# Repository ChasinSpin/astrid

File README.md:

# Astrid (ASTro Imaging Device)

## Introduction

Astrid is a device, software and hardware to record astronomical Occultations, Transits, Eclipses (OTE), and Astrophotography.  Occultations are rare, and having equipment for rare events means that the equipment is unused at other times.  The concept of Astrid is that the device can be used as a general astrophotography camera when occultation work is not being done.  

Astrid compromises of:

* Raspberry Pi 4 Model B - 8GB (4GB untested)
* IMX296 Mono Camera [CAM-MIPI296RAW-Trigger](https://www.inno-maker.com/product/cam-mipi296raw-trigger/)
* [OTEStamper](OTEStamper) Timing board
* Software and Firmware

Astrid has the following features:

* Highly accurate frame timestamping for occultations using GPS
* Global Shutter (Sony IMX296 Sensor Mono)
* Controlled over VNC from Tablet/Computer/Phone (one can control many Astrids)
* Can be paired with a telescope or camera lens
* Audit trail for video
* GPS Position/Altitude
* Plate Solving
* Mount support: [IndiLib](https://indilib.org)
* Focuser support: [IndiLib](https://indilib.org) - Coming Soon
* Goto
* Star Detection
* Stretch
* Uncompressed raw data/video
* .fits file (photos)
* [Raw Astro Video Format (RAVF)](https://github.com/ChasinSpin/ravf) files for video (occultations)
* [PyMovie Support](https://github.com/ChasinSpin/pymovie)
* Dithering
* Multiple Subs
* Occelmnt support
* Occultation metrics
* Unattended Pre-Pointing

## PyMovie

Astrid [Raw Astro Video Format (RAVF)](https://github.com/ChasinSpin/ravf) can be loaded in PyMovie for analysis, using [RAVF PyMovie](https://github.com/ChasinSpin/pymovie).

## Documentation

[Documentation](docs/README.md)

## Obtaining Astrid

Astrid is now being supplied fully built and ready to go from IOTA.  Please see:
[https://occultations.org/astrid-details-and-ordering-page/
](https://occultations.org/astrid-details-and-ordering-page/)

Please note that although Open Source software is free, it is also generally considered good practice to support the time / resources that are donated by authors by purchasing through approved channels like IOTA where available.  That way the software/hardware can continue to be developed. Limited support is also available if one of the approved boards is purchased. 

If you build the board yourself, or it was obtained from another, we are unable to provide support. There has been instances of people making boards, selling them to others for profit and then expecting assistance for free.  We do not have the resources to support these types of ventures.

## Credits

* Steve Preston of IOTA for his invaluable assistance
* Bill Yeung for testing
* Bob Anderson for PyMovie
* Dave Herald - Star Catalogs and Occelmnt
* Hristo Pavlov for OWCloud

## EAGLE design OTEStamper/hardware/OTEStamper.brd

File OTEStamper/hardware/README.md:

## Version 0.9b
	
* Initial

## Version 0.9c

* No electrical changes.
* Moved label for D1 below diode and clarified orientation for the Buck Regulator to make it less likely to assemble wrong way round.

## Version 1.0.0
	
* Added HOT label around buck convertor and back protection FET
* Removed 4 pin flat flex to camera board
* Moved JP2 right to allow clearance of U2
* Moved buzzer to bottom of the board and rotated 45 to make room for 150uF capacitor
* Added 150uF capacitor to limit surge current to regulator
* Moved Fan header so header pins easily clear GPS
* Added JST 2 Pin Connector For Different 12V Source
* Changed Q1/Q2 to MMBT2222A-TP for increased fan current upto 500mA

## Version 1.0.0 (no board revision)

Extended monostable duration from 1.2us to 1ms to account for
different versions of the camera module with varying XVS pulse lengths, which
can cause multiple pulses for each XVS signal:

 * Changed R18 from 1K to 10K
 * Changes C12 from 1nF to 0.1uF

## Future Ideas

1. Maybe look at switching out back protection FET to one with lower RDS as the voltage drop across is large at high currents (buck can keep up fine).

## PSU Characterisation

1. Voltage range is 7.5 - 18V, specified range to the user is 12V-15V @ 4A

2. Voltage dropout occurs at 7.5V

3. Buck starts to current limit (switch the PSU on and off) at 4.1A

4. Max temperature ofr the bucks convert (4A @ 18V) is 130C

5. Damage to the buck convertor will occur at 20V

6. Fuse never gets triggered during normal use.  Would only get trigger if there was failure on the board itself.

| PSU Output | Supply Input | Temperature |
| ---------- | ------------ | ----------- |
| 0.2A @ 5.04V | 0.062A @ 18V | Room |
| 1A @ 5.02V | 0.304A @ 18V | 42C |
| 2A @ 4.97V | 0.604A @ 18V | 57C |
| 3A @ 4.89V | 0.920A @ 18V | 85C |
| 4A @ 4.79V | 1.243A @ 18V | 125C |

## Testing

1. Power at 12V at current limit 40mA, power usage should be approx 25-30mA, GPS LED should be on
2. Test voltage TP1 = Just above 5V
3. Test voltage TP2 = 5V
4. Test in Software with Raspberry Pi and Camera Connected:

	a) Install firmware
	
		make reset
		make writefuses
		make install

	b) Test Buzzer and Fan:
 	
		cd ~/astrid/OTEStamper/test
		./spitest.py
		
	c) Test GPS (and check voltage monitoring)
	
		./spitest_gps.py
	
	d) Record video and check all status buttons are green and video is recorded

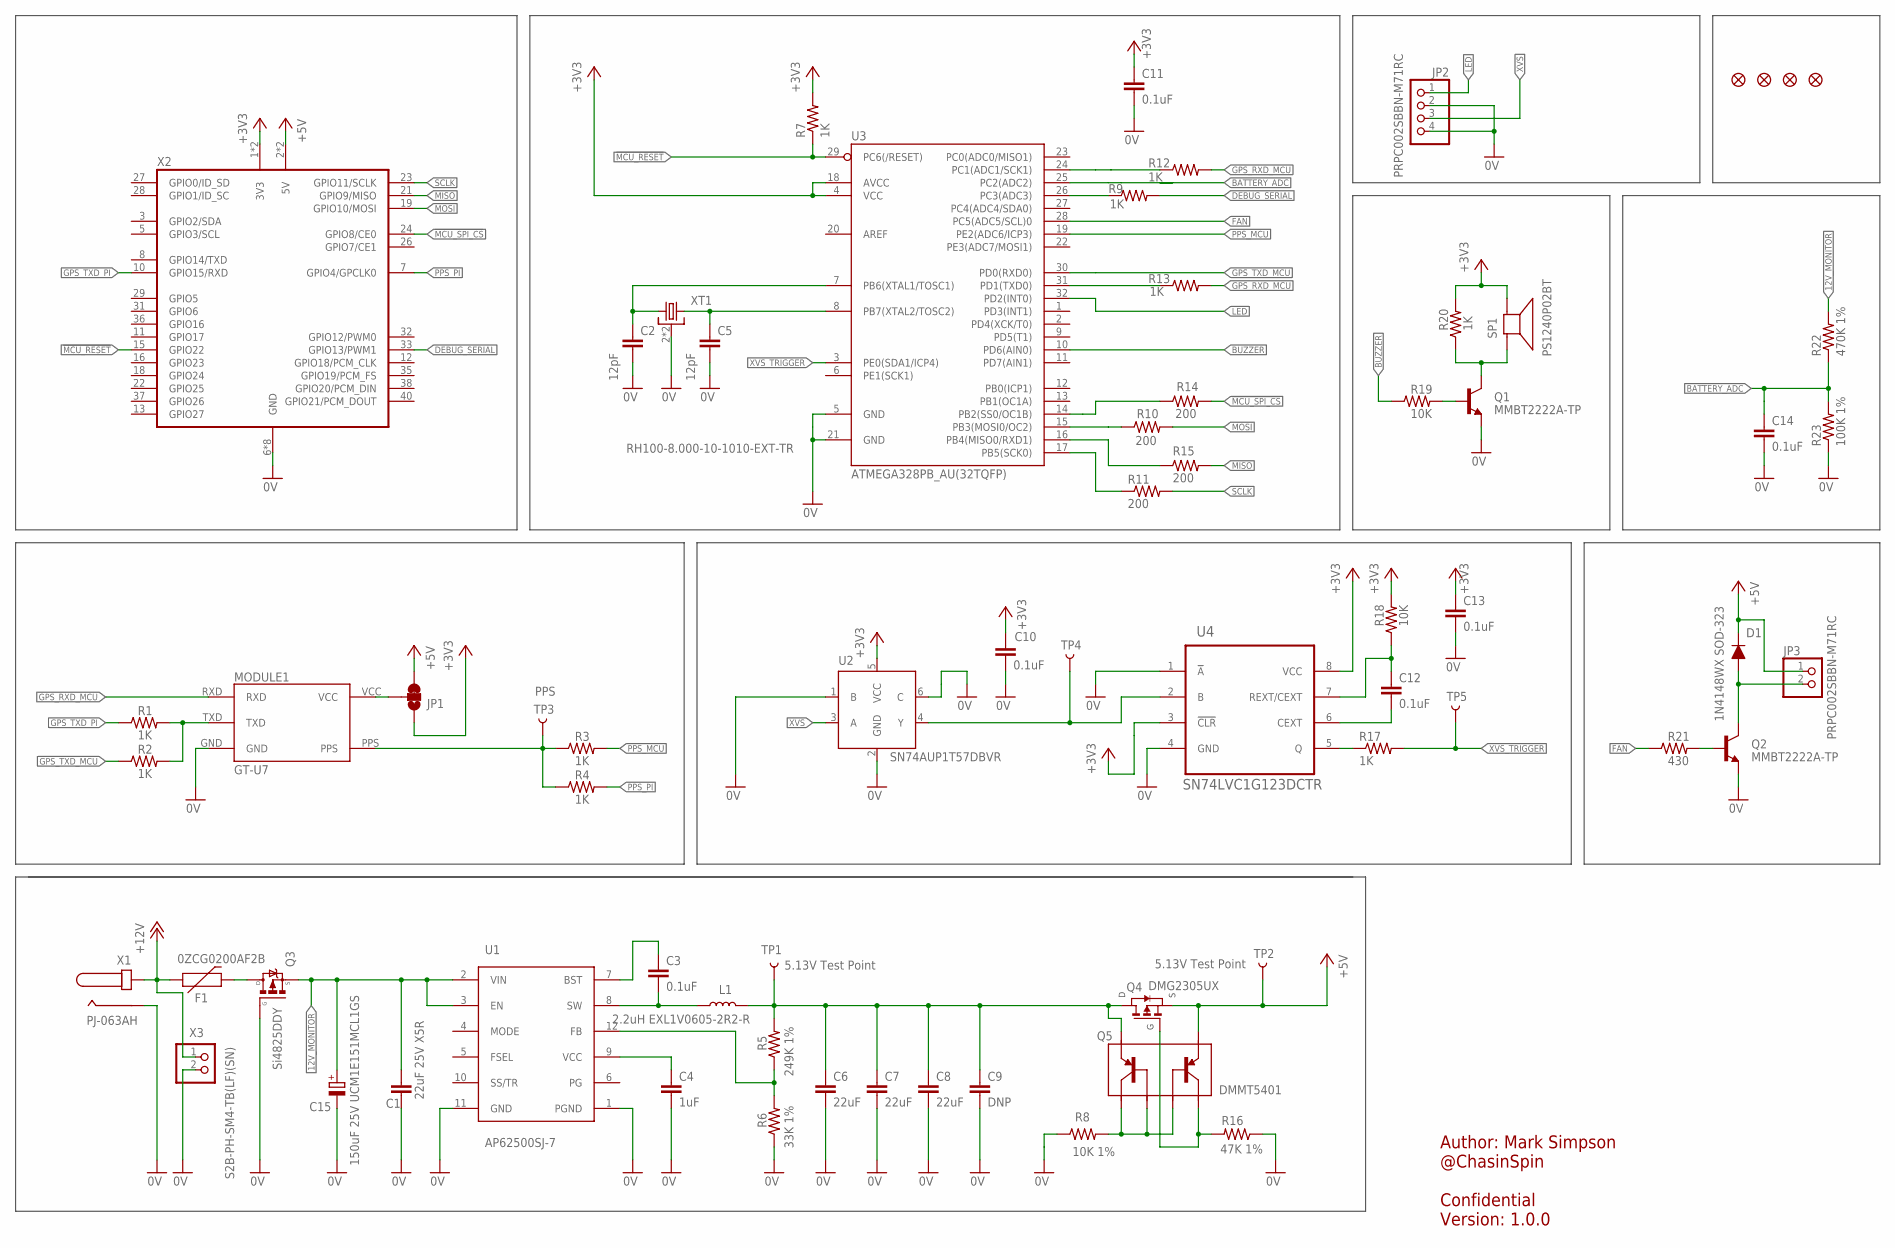
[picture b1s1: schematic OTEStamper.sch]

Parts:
C1: 22uF 25V X5R; C0805K
C2, C5: 12pF; C0603K
C3: 0.1uF; C0402K
C4: 1uF; C0402K
C6, C7, C8: 22uF; C0603K
C9: DNP; C0603K
C10, C11, C12, C13, C14: 0.1uF; C0603K
C15: 150uF 25V UCM1E151MCL1GS; UD-6,3X7,7_NICHICON
D1: 1N4148WX SOD-323; SOD-323
F1: 0ZCG0200AF2B; F1812
FD1, FD2, FD3, FD4: FIDUCIALUFIDUCIAL; FIDUCIAL-MICRO
JP1: JUMPER-SMT_3_1-NC_TRACE_SILK; SMT-JUMPER_3_1-NC_TRACE_SILK
JP2: PRPC002SBBN-M71RC; 1X04
JP3: PRPC002SBBN-M71RC; 1X02
L1: 2.2uH EXL1V0605-2R2-R; EXL1V0605
MODULE1: GT-U7
Q1, Q2: MMBT2222A-TP; SOT23-BEC
Q3: Si4825DDY; SOIC-8-BAR
Q4: DMG2305UX; SI2323DDS
Q5: DMMT5401; SOT26(SC74R)
R1, R2, R3, R4, R7, R9, R12, R13, R17, R20: 1K; R0603
R5: 249K 1%; R0402
R6: 33K 1%; R0402
R8: 10K 1%; R0603
R10, R11, R14, R15: 200; R0603
R16: 47K 1%; R0603
R18, R19: 10K; R0603
R21: 430; R0603
R22: 470K 1%; R0603
R23: 100K 1%; R0603
SP1: PS1240P02BT; PS12
TP1, TP2: 5.13V Test Point; PAD.03X.03
TP3: PPS; PAD.03X.03
TP4, TP5: TEST-POINT3; PAD.03X.03
U1: AP62500SJ-7; AP62500
U2: SN74AUP1T57DBVR; SOT23-6-DBV
U3: ATMEGA328PB_AU(32TQFP); TQFP32-08
U4: SN74LVC1G123DCTR; SSOP-8-DCT
X1: PJ-063AH
X2: ADAFRUIT_2222; RASPBERRY_PI_HAT
X3: S2B-PH-SM4-TB(LF)(SN); JST-PH-2-SMT-RA
XT1: RH100-8.000-10-1010-EXT-TR; ECS-ECX-32

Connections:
0V: C1.2, C2.2, C4.2, C5.2, C6.2, C7.2, C8.2, C9.2, C10.2, C11.2, C13.2, C14.2, C15.-, JP2.2, JP2.4, MODULE1.GND, Q1.E, Q2.E, Q3.4 (G), R6.1, R8.1, R16.1, R23.1, U1.1 (PGND), U1.11 (GND), U2.1 (B), U2.2 (GND), U2.6 (C), U3.5 (GND), U3.21 (GND), U4.1 (!A), U4.4 (GND), X1.2 (NEG), X1.SHIELD1 (NEG), X1.SHIELD2 (NEG), X2.6 (GND), X2.9 (GND), X2.14 (GND), X2.20 (GND), X2.25 (GND), X2.30 (GND), X2.34 (GND), X2.39 (GND), X3.2, XT1.2 (3), XT1.4 (3)
12V_MONITOR: C1.1, C15.+, Q3.1 (S), Q3.2 (S), Q3.3 (S), R22.2, U1.2 (VIN), U1.3 (EN)
!MCU_RESET: R7.1, U3.29 (PC6(/RESET)), X2.15 (GPIO22)
!MCU_SPI_CS: R14.2, X2.24 (GPIO8/CE0)
+3V3: C10.1, C11.1, C13.1, JP1.1, R7.2, R18.2, R20.2, SP1.P$1 (+), U2.5 (VCC), U3.4 (VCC), U3.18 (AVCC), U4.3 (!CLR), U4.8 (VCC), X2.1 (3V3), X2.17 (3V3)
+5V: D1.CATHODE (K), JP1.3, JP3.1, Q4.2 (S), Q5.5 (E2), TP2.P$1, X2.2 (5V), X2.4 (5V)
+12V: F1.1, X1.1 (POS), X3.1
BATTERY_ADC: C14.1, R22.1, R23.2, U3.25 (PC2(ADC2))
BUCK_SW: C3.2, L1.1, U1.8 (SW)
BUCK_VCC: C4.1, U1.9 (VCC)
BUCK_VOUT: C6.1, C7.1, C8.1, C9.1, L1.2, Q4.3 (D), Q5.6 (E1), R5.2, TP1.P$1
BUZZER: R19.1, U3.10 (PD6(AIN0))
DEBUG_SERIAL: R9.2, X2.33 (GPIO13/PWM1)
FAN: R21.1, U3.28 (PC5(ADC5/SCL)0)
FUSE_OUT: F1.2, Q3.5 (D), Q3.6 (D), Q3.7 (D), Q3.8 (D)
GPS_RXD_MCU: MODULE1.RXD, R12.2, R13.2
GPS_TXD_MCU: R2.1, U3.30 (PD0(RXD0))
GPS_TXD_PI: R1.1, X2.10 (GPIO15/RXD)
LED: JP2.1, U3.32 (PD2(INT0))
MCU_SPI_SELECT1: R14.1, U3.14 (PB2(SS0/OC1B))
MISO: R15.2, X2.21 (GPIO9/MISO)
MOSI: R10.2, X2.19 (GPIO10/MOSI)
unnamed: R9.1, U3.26 (PC3(ADC3))
unnamed: MODULE1.PPS, R3.1, R4.1, TP3.P$1
unnamed: D1.ANODE (A), JP3.2, Q2.C
unnamed: Q2.B, R21.2
unnamed: C3.1, U1.7 (BST)
unnamed: R5.1, R6.2, U1.12 (FB)
unnamed: Q1.B, R19.2
unnamed: Q1.C, R20.1, SP1.P$2 (-)
unnamed: MODULE1.TXD, R1.2, R2.2
unnamed: JP1.2, MODULE1.VCC
unnamed: R17.1, U4.5 (Q)
unnamed: TP4.P$1, U2.4 (Y), U4.2 (B)
unnamed: C12.2, U4.6 (CEXT)
unnamed: C12.1, R18.1, U4.7 (REXT/CEXT)
unnamed: C2.1, U3.7 (PB6(XTAL1/TOSC1)), XT1.1
unnamed: C5.1, U3.8 (PB7(XTAL2/TOSC2)), XT1.3 (2)
unnamed: R10.1, U3.15 (PB3(MOSI0/OC2))
unnamed: R15.1, U3.16 (PB4(MISO0/RXD1))
unnamed: R11.1, U3.17 (PB5(SCK0))
unnamed: R13.1, U3.31 (PD1(TXD0))
unnamed: R12.1, U3.24 (PC1(ADC1/SCK1))
unnamed: Q5.1 (C1), Q5.2 (B1), Q5.3 (B2), R8.2
unnamed: Q4.1 (G), Q5.4 (C2), R16.2
PPS_MCU: R3.2, U3.19 (PE2(ADC6/ICP3))
PPS_PI: R4.2, X2.7 (GPIO4/GPCLK0)
SCLK: R11.2, X2.23 (GPIO11/SCLK)
XVS: JP2.3, U2.3 (A)
XVS_TRIGGER: R17.2, TP5.P$1, U3.3 (PE0(SDA1/ICP4))

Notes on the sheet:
Author: Mark Simpson @ChasinSpin Confidential Version: 1.0.0

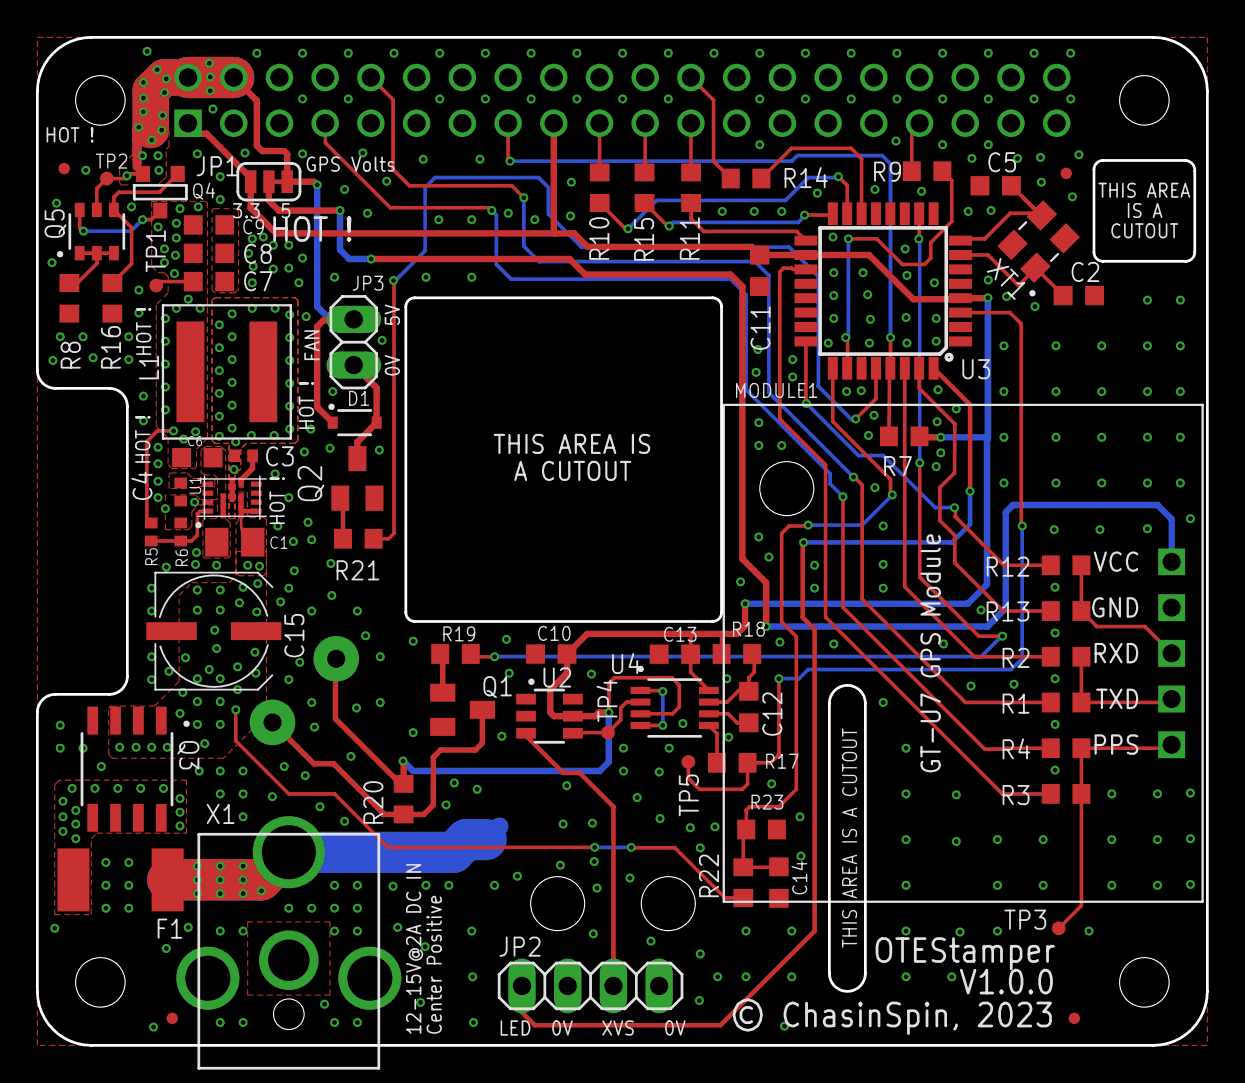
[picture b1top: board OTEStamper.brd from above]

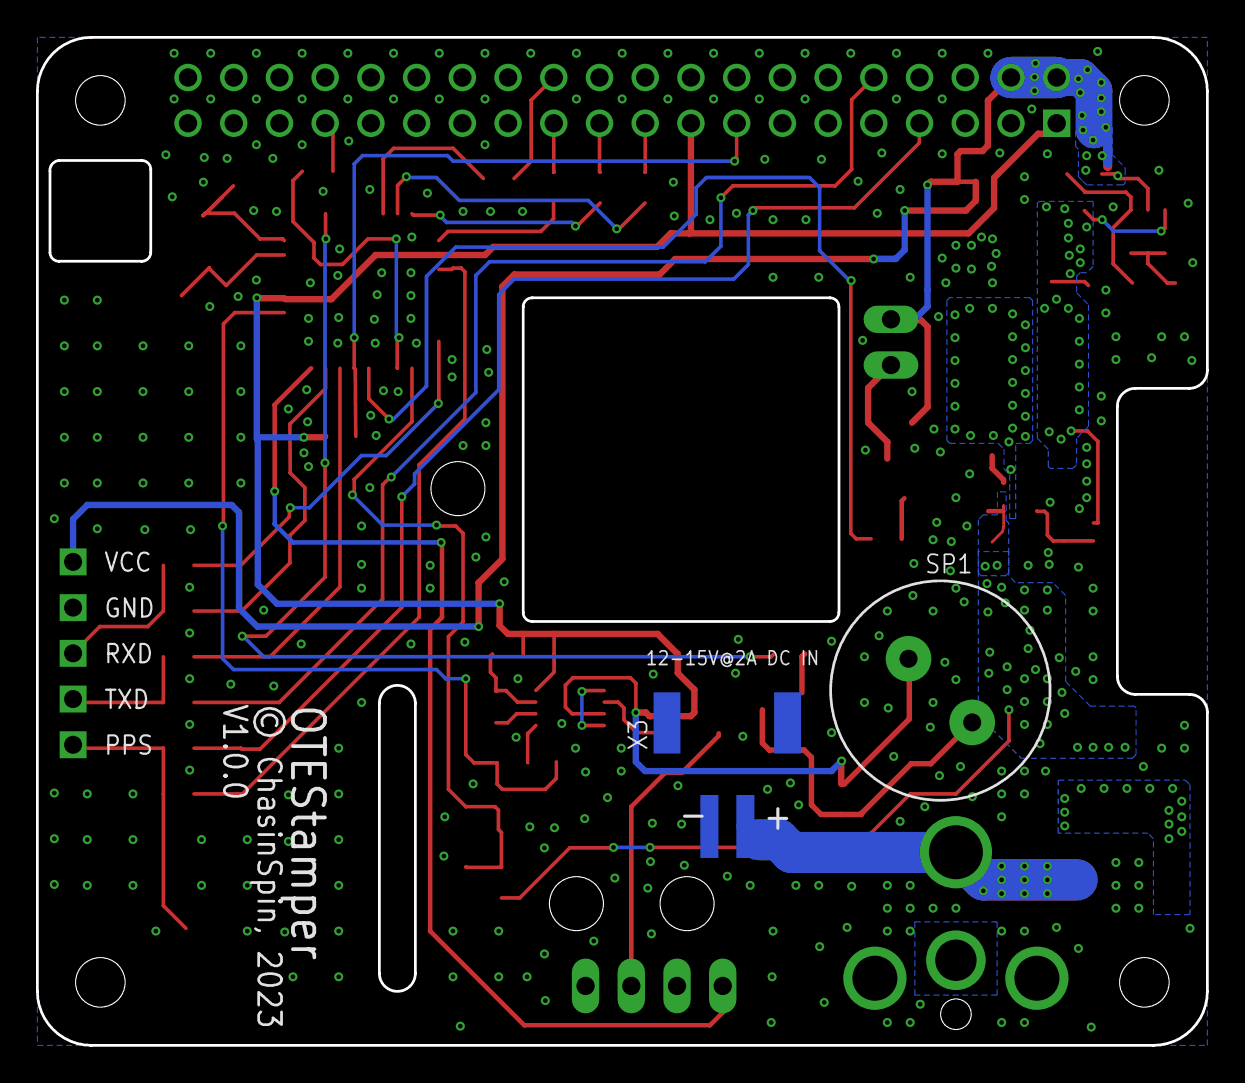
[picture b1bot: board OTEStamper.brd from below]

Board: 2 copper layers, 65.0 x 56.0 mm, 68 parts (2 on the bottom side), 50 nets.

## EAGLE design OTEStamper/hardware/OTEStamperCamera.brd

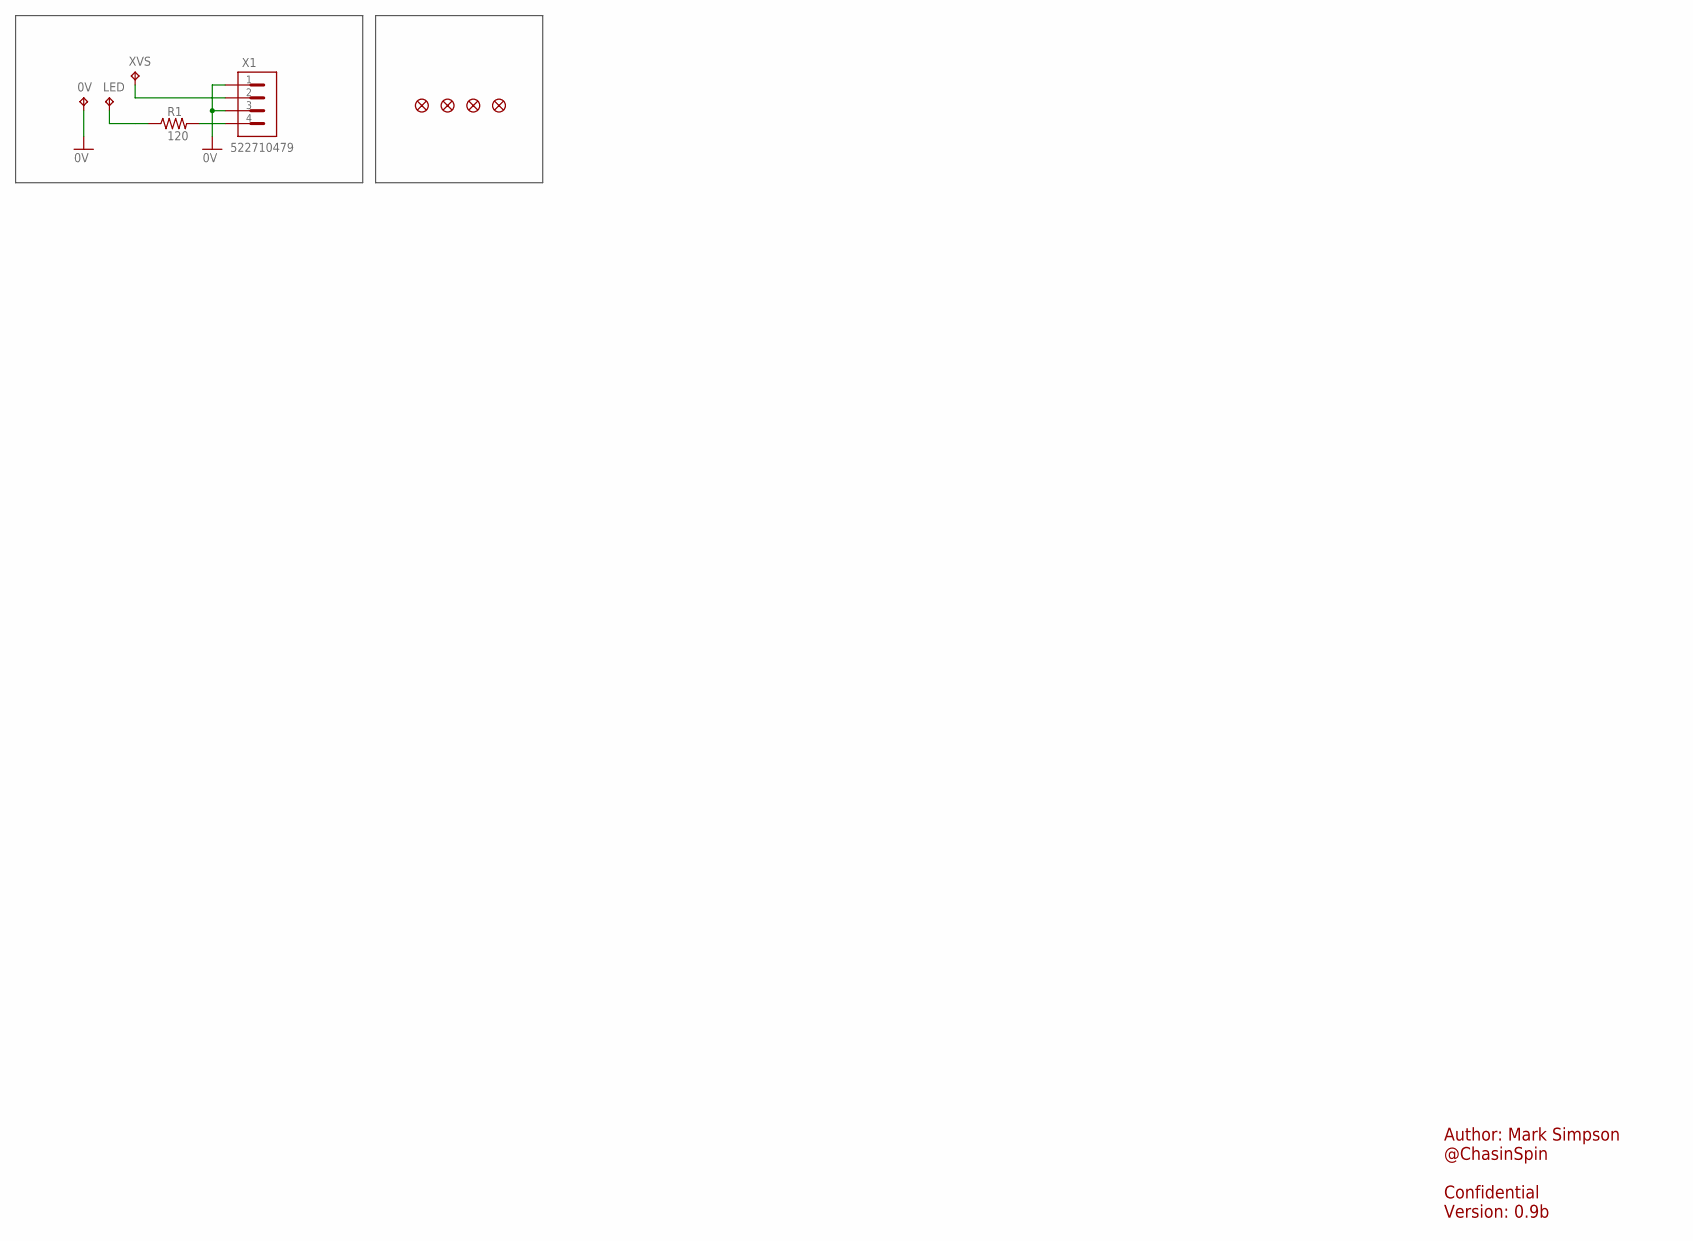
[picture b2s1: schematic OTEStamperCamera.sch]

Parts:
0V: LED; TP16SQ
FD1, FD2, FD3, FD4: FIDUCIALUFIDUCIAL; FIDUCIAL-MICRO
LED: LED; TP16SQ
R1: 120; R0603
X1: 522710479
XVS: TPTP16SQ; TP16SQ

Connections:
0V: 0V.TP, X1.1, X1.3
unnamed: R1.2, X1.4
unnamed: X1.2, XVS.TP
unnamed: LED.TP, R1.1

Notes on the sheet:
Author: Mark Simpson @ChasinSpin Confidential Version: 0.9b

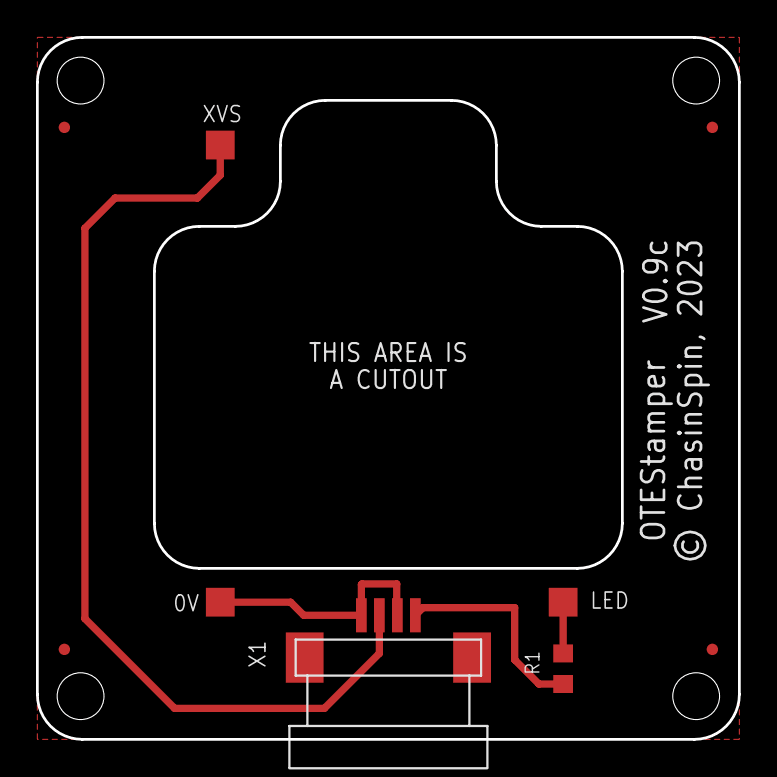
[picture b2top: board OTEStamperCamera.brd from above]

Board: 2 copper layers, 39.0 x 39.0 mm, 9 parts (0 on the bottom side), 4 nets.

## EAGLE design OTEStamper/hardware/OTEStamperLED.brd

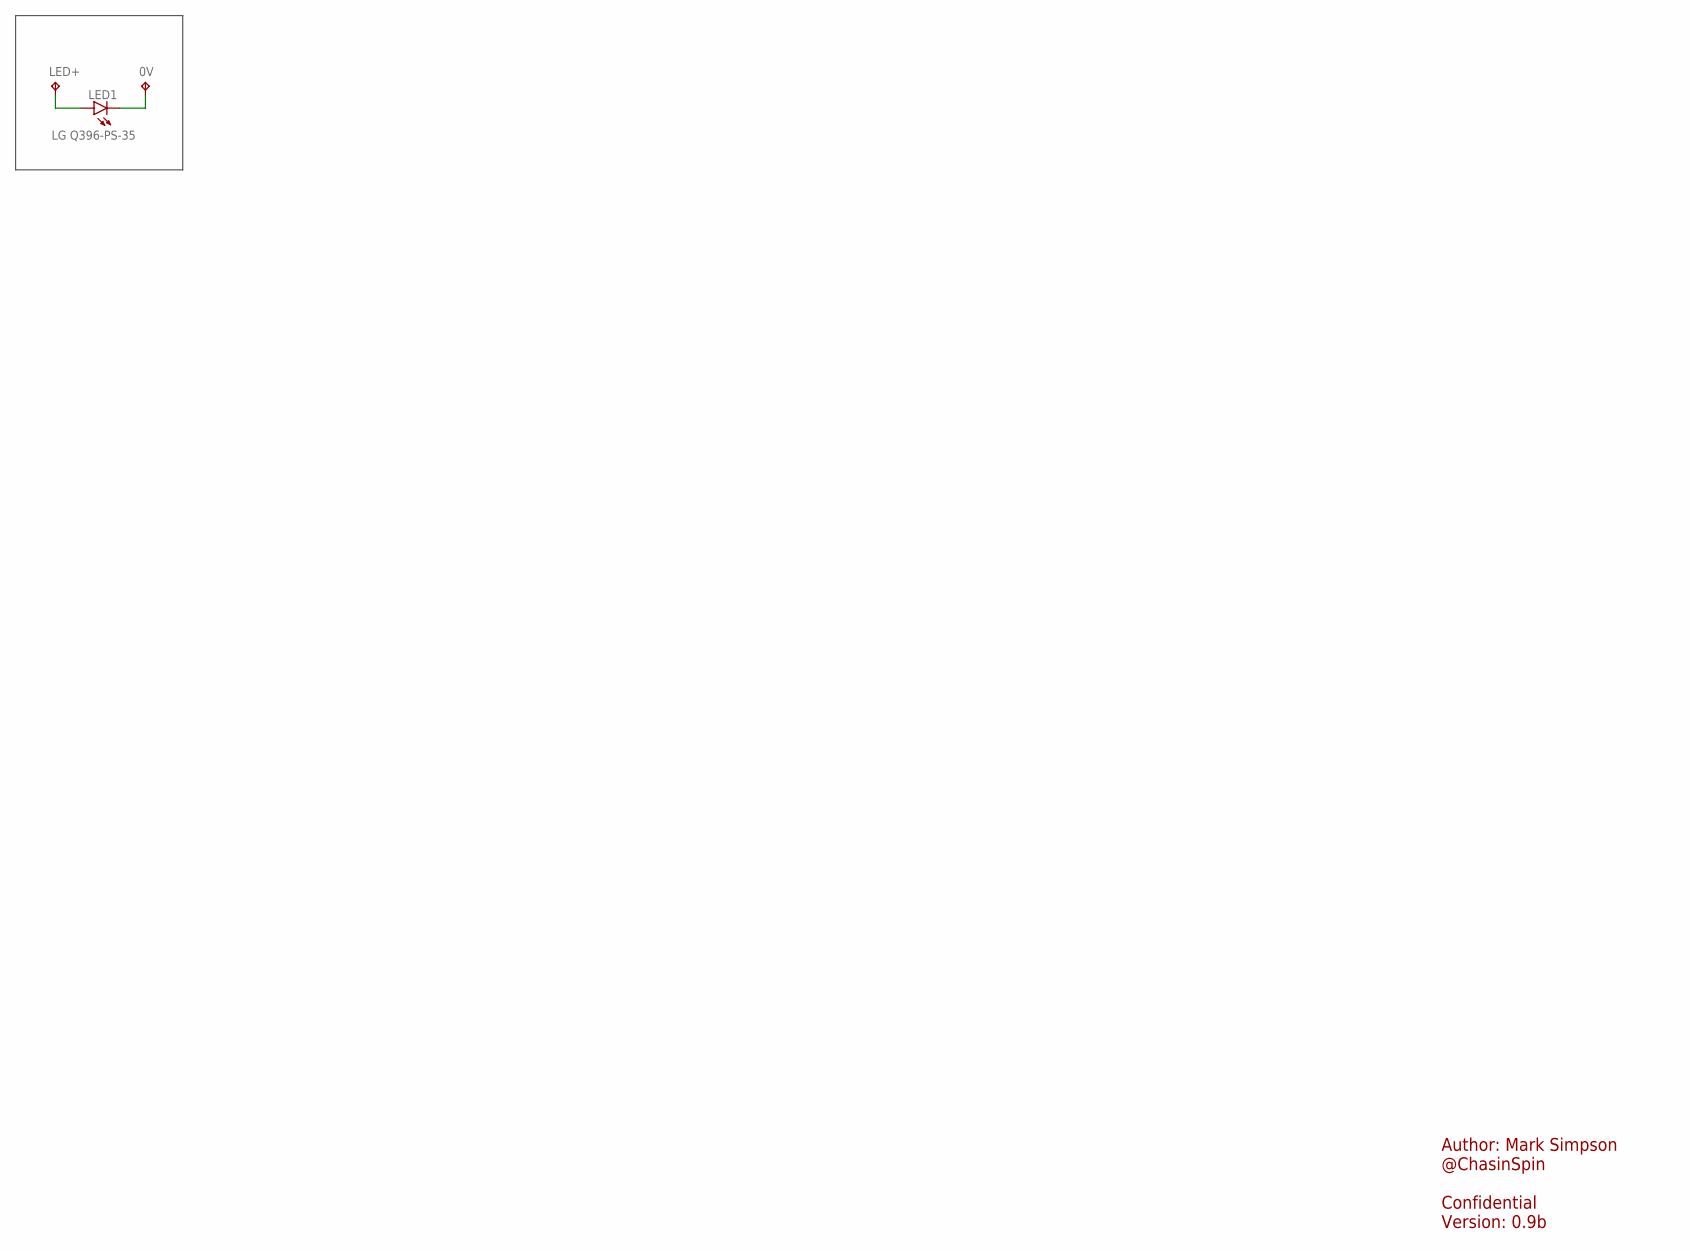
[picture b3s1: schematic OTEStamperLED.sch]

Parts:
0V: LED; TP16SQ
LED1: LG Q396-PS-35; CHIP-LED0603
LED+: LED; TP16SQ

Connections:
unnamed: LED1.A, LED+.TP
unnamed: 0V.TP, LED1.C

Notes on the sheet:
Author: Mark Simpson @ChasinSpin Confidential Version: 0.9b

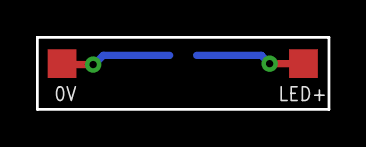
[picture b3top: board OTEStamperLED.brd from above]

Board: 2 copper layers, 16.2 x 4.0 mm, 3 parts (1 on the bottom side), 2 nets.

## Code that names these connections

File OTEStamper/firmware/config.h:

#define FIRMWARE_VERSION	0x0001
#define OTESTAMPER_ID		0xFD032A1C



//IMPORTANT: When debug is enabled, FRAME Interrupts are disabled
//#define DEBUG

#define F_CPU 8000000L

#define PIN_LED_PORT		PORTD
#define PIN_LED_PIN		PIND
#define PIN_LED_DDR		DDRD
#define PIN_LED_BIT		_BV(PD2)

#define PIN_FRAME_INT_PORT	PORTC
#define PIN_FRAME_INT_PIN	PINC
#define PIN_FRAME_INT_DDR	DDRC
#define PIN_FRAME_INT_BIT	_BV(PC3)

#define PIN_DEBUG_PORT		PIN_FRAME_INT_PORT
#define PIN_DEBUG_PIN		PIN_FRAME_INT_PIN
#define PIN_DEBUG_DDR		PIN_FRAME_INT_DDR
#define PIN_DEBUG_BIT		PIN_FRAME_INT_BIT

#define PIN_SPI_MISO_PORT	PORTB
#define PIN_SPI_MISO_PIN	PINB
#define PIN_SPI_MISO_DDR	DDRB
#define PIN_SPI_MISO_BIT	_BV(PB4)

#define PIN_SPI_MOSI_PORT	PORTB
#define PIN_SPI_MOSI_PIN	PINB
#define PIN_SPI_MOSI_DDR	DDRB
#define PIN_SPI_MOSI_BIT	_BV(PB3)

#define PIN_SPI_SCLK_PORT	PORTB
#define PIN_SPI_SCLK_PIN	PINB
#define PIN_SPI_SCLK_DDR	DDRB
#define PIN_SPI_SCLK_BIT	_BV(PB5)

#define PIN_SPI_CS_PORT		PORTB
#define PIN_SPI_CS_PIN		PINB
#define PIN_SPI_CS_DDR		DDRB
#define PIN_SPI_CS_BIT		_BV(PB2)

#define PIN_PPS_PORT		PORTD
#define PIN_PPS_PIN		PIND
#define PIN_PPS_DDR		DDRD
#define PIN_PPS_BIT		_BV(PD2)

#define PIN_XVS_PORT		PORTD
#define PIN_XVS_PIN		PIND
#define PIN_XVS_DDR		DDRD
#define PIN_XVS_BIT		_BV(PD3)

#define PIN_BUZZER_PORT		PORTD
#define PIN_BUZZER_PIN		PIND
#define PIN_BUZZER_DDR		DDRD
#define PIN_BUZZER_BIT		_BV(PD6)

#define PIN_FAN_PORT		PORTC
#define PIN_FAN_PIN		PINC
#define PIN_FAN_DDR		DDRC
#define PIN_FAN_BIT		_BV(PC5)

#define DEBUG_BAUD_RATE		9600

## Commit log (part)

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2023-09-29 Updating format for USB Flash Drive
2023-09-29 Adding more configs
2023-09-30 Phase 1 of Settings Auto Update working
2023-10-01 Updating documentation for new settings
2023-10-01 Change Stylesheet to macro based with astro colorscheme json in preparation for multiple color schemes
2023-10-01 Updating version
2023-10-02 Video frame rates <= 10fps now have full frame stretch
2023-10-03 Moving display code from CameraModel into DisplayOps
2023-10-06 Updating BOM for V1.0.0 board
2023-10-06 For polar align test mode and platesolving, now displays the images after selection
2023-10-06 Adding star detection, HFD
2023-10-08 Smaller font for HFD measurements
2023-10-09 Adding start of OWCloud support
2023-10-09 Typo
2023-10-10 Implementing next stage of Astrid Player
2023-10-10 Fixing Player icon on desktop
2023-10-11 Fixing bugs with no GPS and bad occelmnt
2023-10-11 Now defaults to Occultations for the Object Database on launch
2023-10-11 Updating TODO
2023-10-22 Adding FAN test
2023-10-22 Extending XVS monostable pulse extender from 1.2uS to 1ms, to account for different camera boards with different XVS pulse lengths.
2023-10-26 Updating documentation, improving case design
2023-10-27 Added message box when user changes config.
2023-10-27 Making font smaller on splashes
2023-10-28 Updating path computation
2023-10-28 Updating docs
2023-10-28 Making general setting per config
2023-10-28 Adding Power Supply Voltage Monitoring
2023-10-29 Occultations can now be downloaded from OWCloud
2023-10-29 Adding GPS Fuzzing
2023-11-01 Adding FAQ
2023-11-01 Removed .DS_Store which was preventing AstridUSB from getting deleted during USB Drive Format
2023-11-02 Updating OWCloud import to import occelmnt
2023-11-02 Added switching hardware acceleration in chrome off in upgrade.sh
2023-11-02 Fixing permission error in install.sh for OS notification disable
2023-11-02 Adding source (OWCloud or User) for the source of the occultations. Changed OWCloud from import to Sync. OWCloud occultations are now deleted when new ones are imported.
2023-11-03 Fixed error with voltage not set
2023-11-04 Adding Occeltation XML search. This is an interim checkin for backup, not working yet
2023-11-04 Changing pressure to 0, as altitudes below 5deg in AltAz conversions are numerically unstable
2023-11-05 Can now click on and add an occultation
2023-11-05 Added disable file manager from popping up when USB Drive is inserted
2023-11-06 Fixed thread killing. This should improve things, time will tell.
2023-11-06 Added the divide by 2.0 back in
2023-11-06 Adding Star Catalog
2023-11-07 Search by Gaia source id now working in the star catalog
2023-11-07 Updating owcloud syncing for new url provided by Hristo
2023-11-08 Fixing bug with source key not existing
2023-11-08 Fixing thread bug in platesolver
2023-11-13 Adding annotation
2023-11-16 Added sanitization for jobs names so jobs with space and period get translated to underscore
2023-11-16 Updating install.sh
2023-11-16 Adding battery cover
2023-11-16 Adding automatic extraction
2023-11-17 Exit for shutdown now has a timer, and instructions on properly shutting down
2023-11-18 First pass at Solar System database
2023-11-18 Updating to GCRS again for planets
2023-11-28 Merging development branch back in after testing
2023-11-28 Adding Metadata button to player
2023-11-29 Don't add expired occultations when OW syncing
2023-12-03 Adding print to indicate fix to the last commit
2023-12-04 Adding automatic filling of North American Occultation Report Form
2023-12-05 When an object is searched and found, the job name is now updated to match
2023-12-17 Adding version management
2023-12-17 Adding Astrid Version number to "Choose Config" dialog
2023-12-18 Moving UTC Time from Display 1 to Status panel
2023-12-18 Updating releasenotes
2023-12-18 Added frame timestamp to player
2023-12-18 Adding privacy policy
2023-12-18 Added "Save Fits Finder" to Player, which can be used after a plate solver to identify the target. This can be loaded as a finder image into pymovie to make it easy to place targets. Improved constra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
2023-12-19 Fixed bug where Astrid bombs when fits file does not contains FOCALLEN
2023-12-21 Upping frame rate to 5000fps for video for daylight focusing
2023-12-23 Fixed floating point and integer validators in fields to process incomplete entries better
2023-12-30 Reduced startup time with no internet by 5 seconds Timing Status Button is now red when system time differs from GPS time by more than 2 second GPS Time/System Time difference split out to Delta Chro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
2023-12-31 Added object target crosshairs
2023-12-31 All mounts now switch tracking on after a goto prepoint and immediately off so that slew complete can be detected
2023-12-31 Derated GPS/Timing/Acquition to permit recording when yellow too
2024-01-03 Increased allowable system time / gps time delta from 2 to 30 seconds
2024-01-03 Added "This report was pre-populated by Astrid" the north american report form
2024-01-05 North American Report AutoFill has some fields as text that should be numbers for auto processing by IOTA
2024-01-05 Release 1.0.13
2024-01-16 Updating Power Supply document
2024-01-23 Updating arg
2024-01-30 Updating mount documentation for SE6/SE8
2024-02-03 Added MagRP and MagBP to last checkin to give some estimation of spectral type for comparison
2024-02-07 2nd try at getting the download link to work
2024-02-07 Updating troubleshooting
2024-02-16 Added error reporting to acquisition for dropped shared memory frames due to all the frame buffers being used Fixed bug where errors during recording prevent recording being stopped
2024-02-16 Releasing version 016
2024-02-18 Updating version to 017
2024-02-22 Updating to version 018
2024-03-17 Adding mini display case
2024-03-17 Removed some redundant code in CameraModel Reduced suggested maximum frame rate to 20fps for now because of Sandisk USB Drive Non Compliance
2024-03-20 Added diagnostics primarily to test USB Drives
2024-03-20 Added checks and warnings for USB drives that are not UASP and/or USB3 compliant on Astrid Startup and also when using manual recording. Bug fix to diagnostics.sh,
2024-03-21 Updates USB Thumb drive recommendations
2024-03-26 Adding ravf_integrate.py (no changes to Astrid App)
2024-03-26 Fixing last commit
2024-03-26 Improved Player Icon
2024-03-26 Updating PlayerIcon.png
2024-03-31 Added autorepair to corrupt .ravf's in Player
2024-04-03 Updating for InstallMiniDisplay script for desktop
2024-04-03 Removed printing from astridmonitor in preparation for becoming a daemon. Added adafruit-board-toolkit python module to installer
2024-04-03 Added message about the reset button to Install Mini Display
2024-04-03 Fixing service initialization in install.sh
2024-04-04 Renamed KillAstrid to Terminate Astrid Threads Added Shutdown Icon to desktop
2024-04-04 Released version 1.0.025 Amended CameraModel for /dev/tty/ACM* mounts to exclude Mini Display
2024-04-04 Updated Mini Display to display switching on button press. 1.0.026 release
2024-04-05 Fixing bug with Mini Display drive being picked up on the drive speed check at start instead of the Astrid Drive
2024-04-06 Adding binaries and documentation for Adafruit ESP32-S3 Reverse TFT Feather support for the MiniDisplay
2024-04-07 Interim checkin for new writetest/qualify_drive
2024-04-11 Improving drive identification code
2024-04-12 diagnostics.sh now no longer picks up the Mini Display
2024-04-13 Added Qualify Drive
2024-04-14 Eeprom is now saved (Fuse EESAVE) across Astrid Upgrades, which speeds up time to record after upgrade if Leap Seconds is stored in eeprom Warning now appears when switching off Full Sky Solve to pre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
2024-04-16 Added "Export OWCloud Locations" to Occultations List to speed up multi-chord deployments
2024-04-21 Fix a bug, where having internet and then not having internet when an IERS update is rerequired can cause astrid to stop
2024-04-21 Fixed a bug that caused astrid to stop when a configuration with a goto mount was being used, but no mount was connected
2024-04-21 Photo acquisition now maintains contrast when display options are changed Image flipping is now maintained when display options are changed
2024-04-21 Fix to last checkin to remove print's which slow down acquisition
2024-04-22 Added auto stretches (Histogram Equalization, CLAHE and MinMax Presets/Custom)
2024-04-22 Updating to 1.0.034
2024-04-22 Added OCCULTATION-PREDICTED-CENTER-TIME-FULL to ravf metadata that includes microseconds for the predicted center time
2024-04-24 Fixed bug in player where ravf_integrated videos didn't load in player (also requires new ravf version)
2024-08-01 Updating Troubleshooting doc
2024-08-01 Updating iotaconfigure
2024-08-01 Updating permissions for cleanship.sh
2024-08-01 Added scripts to make installing image and cleaning for shipping, easier for Ted
2024-08-08 Adding LightsOut to Astrid Tools to switch ethernet and power/activity lights off and on
2024-08-11 Generating stl's
2024-08-24 Updating Mouts document
2024-08-24 Updating FAQ and TODO
2024-09-06 Updating for FDM Printing and adding a 2nd case for Prime Focus
2024-09-06 Prepoint window is now further to the left of the video window
2024-09-06 On the Auto Record panel (and other panels where date/time editing is disabled), the up/down arrows have been removed for clarity
2024-09-06 Updating version to 1.0.41
2024-09-08 Fixed bug that was reintroduced by change in 1.0.042, where if the occultation target wasn't goto'd, the RA/DEC of the target were not recorded in the .ravf metadata, preventing the target identifica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
2024-09-09 Updating Prime Focus imagte
2024-09-11 Added documentation about ethernet connections.
2024-09-12 Adding SettingsAndCalibrationForOccultations to documentation
2024-09-19 Added automatic removal of bad ASTRID drive mount point caused by power removal without shutdown
2024-09-19 Mount settings for indi module and usb tty are now constrained to a choice list. Mismatch between indi driver name and settings driver name is now detected and prompted to auto fix
2024-09-20 Fixing previous checking
2024-09-21 Releasing version 1.0.44
2024-09-29 Adding case2 collars and updating case1 for ASA Black
2024-12-09 Fixed issue with Polar Align exception at end of polar align routine introduced in V 1.0.044
2025-01-20 Unifying case1 and case2 into case2 and reorganizing 3D printed files to make it clearer
2025-01-22 Added exposure to "Other Detector related info" field in the North American Report Form as per request from Steve Conard
2025-02-04 Updated 3DPrinting files
2025-02-18 Fixed issue introduced in 1.0.047, where Player failed during platesolving due to logging changes
2025-02-18 Adding set time/set site to settings/mounts, for mounts that don't play nice with these settings
2025-02-18 Updating release notes and version
2025-02-23 Added the capability to wirelessly connect to mounts. Wifi/ethernet capability added. Note: Network connections to mounts maybe unreliable and are unsupported. See mount settings
2025-03-15 Settings now survive a USB Drive Full when being written
2025-03-16 Fixed bug introduced in version 1.0.050 which caused focus settings not to be created
2025-04-05 Added satellite positioning capability with TLE download via space-track.org. See Space-Track settings and new satellite database.
2025-04-08 Fixed issue with Custom Objects not being found
2025-10-02 Fixed error handling on connecting to OWCloud when internet is not available, it now produces an appropriate error
2026-04-09 Adding ability to poweroff Astrid from Mini Display by pressing the bottom left button

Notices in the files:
OTEStamper/hardware/OTEStamper.brd:
© ChasinSpin, 2023
